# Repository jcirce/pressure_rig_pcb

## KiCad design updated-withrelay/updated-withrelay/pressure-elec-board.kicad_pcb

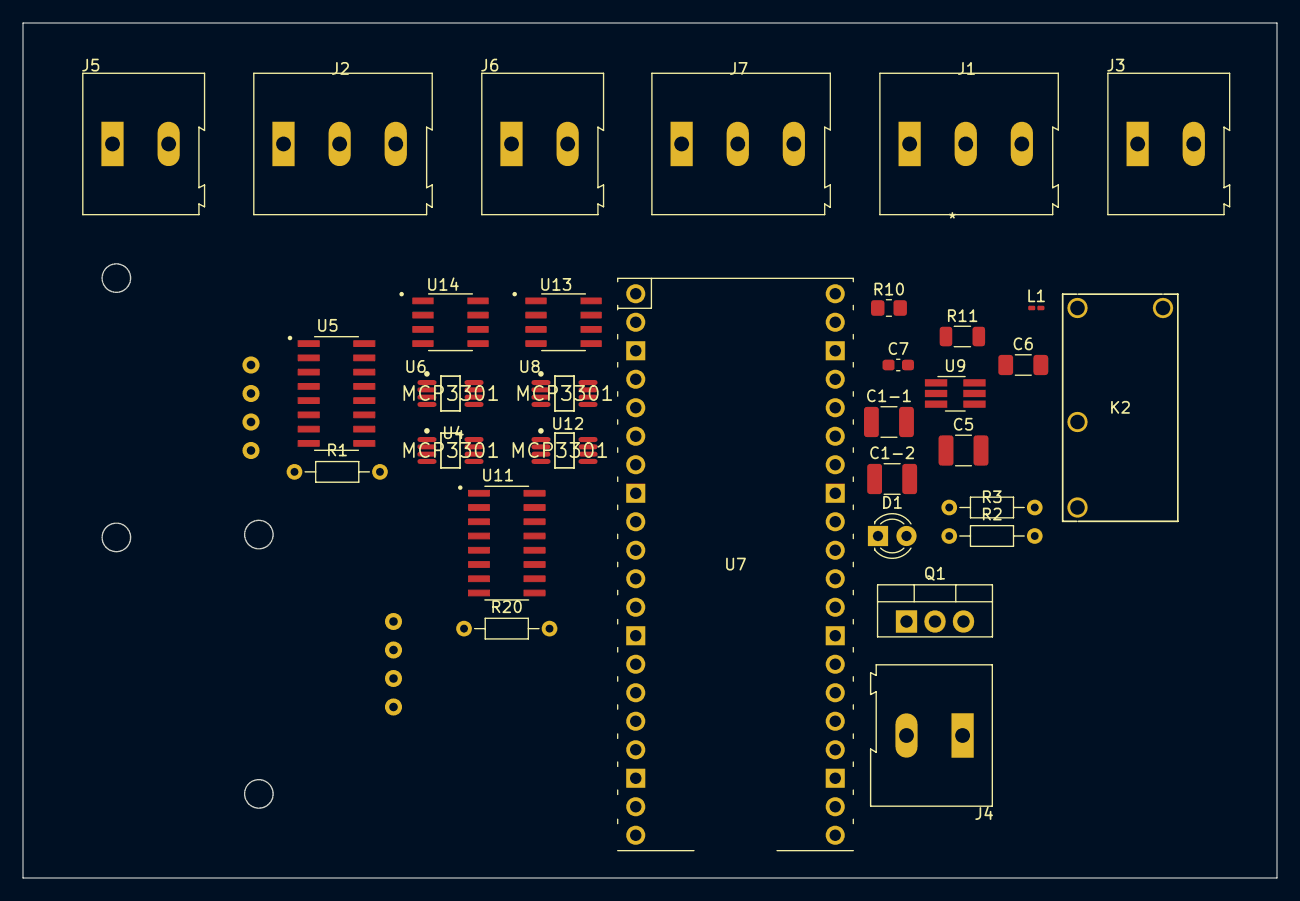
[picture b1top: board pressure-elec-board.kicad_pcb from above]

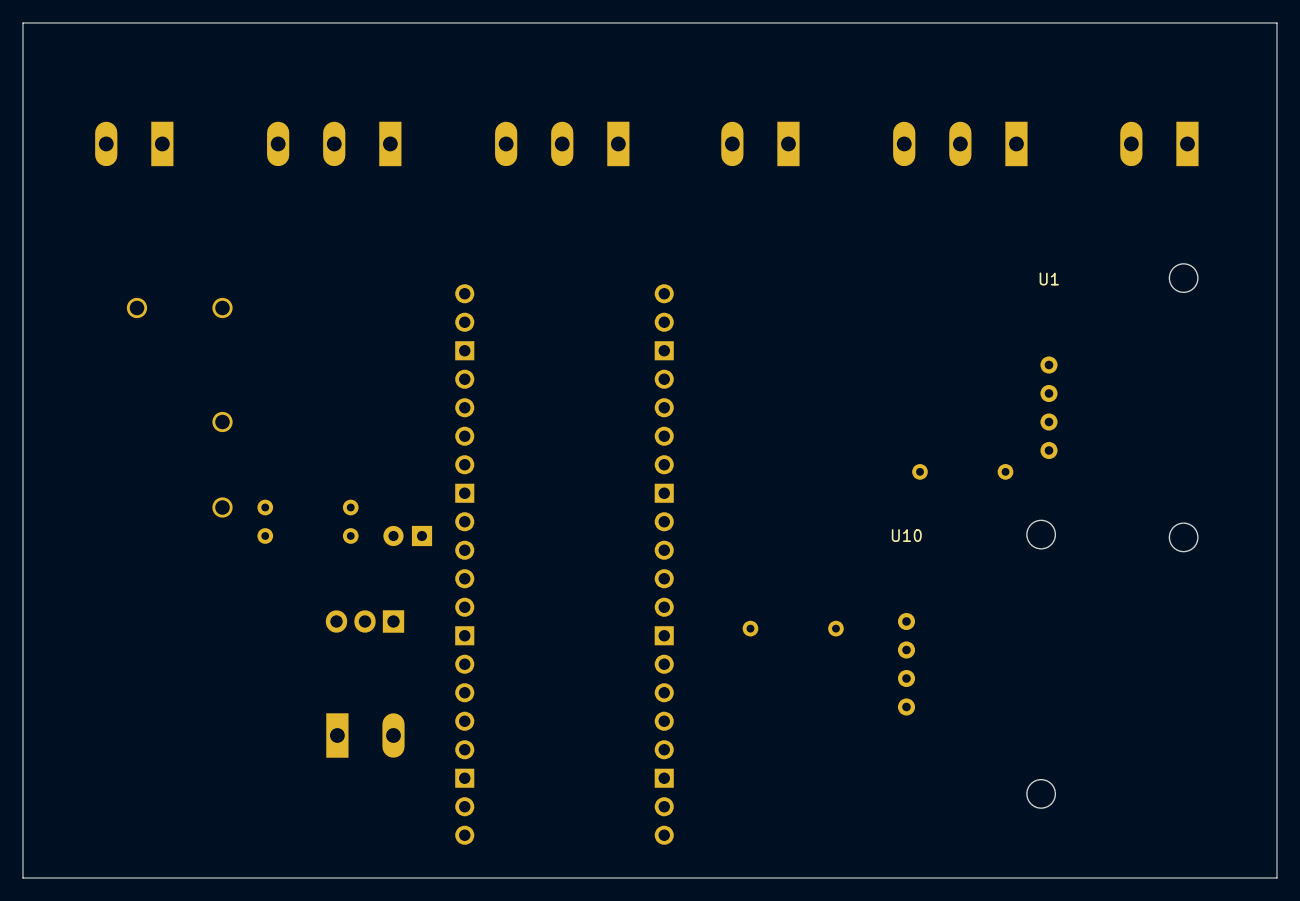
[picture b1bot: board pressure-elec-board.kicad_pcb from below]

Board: 2 copper layers, 111.7 x 76.2 mm, 34 parts (2 on the bottom side), 32 nets, no tracks yet.

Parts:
C1-1, C1-2: 22μ; C_1210_3225Metric_Pad1.33x2.70mm_HandSolder
C5: 10μ; C_1210_3225Metric_Pad1.33x2.70mm_HandSolder
C6: 0.1μ; C_1206_3216Metric_Pad1.33x1.80mm_HandSolder
C7: 47p; C_0603_1608Metric_Pad1.08x0.95mm_HandSolder
D1: LED; LED_D3.0mm
J1, J2, J7: Screw_Terminal_01x03; TerminalBlock_Altech_AK300-3_P5.00mm
J3, J4, J5, J6: Screw_Terminal_01x03; TerminalBlock_Altech_AK300-2_P5.00mm
K2: ALQ305; RELAY_ALQ3_PAN
L1: 4.7u; L_0201_0603Metric_Pad0.64x0.40mm_HandSolder
Q1: IRF540N; TO-220-3_Vertical
R1, R20: 810; R_Axial_DIN0204_L3.6mm_D1.6mm_P7.62mm_Horizontal
R2: 10k; R_Axial_DIN0204_L3.6mm_D1.6mm_P7.62mm_Horizontal
R3: 220; R_Axial_DIN0204_L3.6mm_D1.6mm_P7.62mm_Horizontal
R10: 158k; R_0805_2012Metric_Pad1.20x1.40mm_HandSolder
R11: 30.1k; R_1206_3216Metric
U1, U10: mpx2200; MPX2200
U4, U6, U8, U12: MCP3301; Microchip-MCP3301-BI_MS-Level_B
U5, U11: INA125P; SOIC127P600X175-16N
U7: PicoW; RPi_Pico_SMD_TH
U9: AP63300WU-7; TSOT-23-6_HandSoldering
U13, U14: MCP4921-EP; SOIC127P600X175-8N

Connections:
3.3V: U7.36 (3V3), U13.1 (VDD), U13.6 (VrefA), U14.1 (VDD), U14.6 (VrefA)
5V: D1.2 (A), J4.1, U1.3 (V_supply), U4.1 (Vref), U4.8 (Vdd), U5.1 (V+), U5.2 (~SLEEP), U6.1 (Vref), U6.8 (Vdd), U8.1 (Vref), U8.8 (Vdd), U10.3 (V_supply), U11.1 (V+), U11.2 (~SLEEP), U12.1 (Vref), U12.8 (Vdd)
12V: C5.1, J1.1, U9.2 (EN), U9.3 (VIN)
+5V: C1-1.1, C1-2.1, C7.2, L1.2, R10.2, U7.39 (VSYS)
ADC_1_ACTIVE: U6.5 (~CS/SHDN), U7.15 (GPIO11), U8.5 (~CS/SHDN), U12.5 (~CS/SHDN)
ADC_2_ACTIVE: U4.5 (~CS/SHDN), U7.14 (GPIO10)
CLK: U4.7 (CLK), U6.7 (CLK), U7.4 (GPIO2), U7.9 (GPIO6), U8.7 (CLK), U12.7 (CLK), U13.3 (SCK), U14.3 (SCK)
DAC_ACTIVE: U13.2 (~CS), U14.2 (~CS)
GND: C1-1.2, C1-2.2, C5.2, J1.2, J5.2, J6.2, Q1.3 (S), R2.2, R3.2, R11.2, U1.1 (GND), U4.3 (IN-), U4.4 (Vss), U5.3 (V-), U5.5 (IAREF), U5.12 (VREFCOM), U6.3 (IN-), U6.4 (Vss), U7.3 (GND), U7.8 (GND), U7.13 (GND), U7.18 (GND), U7.23 (GND), U7.28 (GND), U8.3 (IN-), U8.4 (Vss), U9.4 (GND), U10.1 (GND), U11.3 (V-), U11.5 (IAREF), U11.12 (VREFCOM), U12.3 (IN-), U12.4 (Vss), U13.5 (~LDAC), U13.7 (AVSS), U14.5 (~LDAC), U14.7 (AVSS)
GPIO5: Q1.1 (G), R2.1, U7.29 (GPIO22)
MISO_3V_reg1: U7.6 (GPIO4), U8.6 (Dout)
MISO_3V_reg2: U4.6 (Dout), U7.11 (GPIO8)
MOSI_reg1: U7.5 (GPIO3), U14.4 (SDI)
MOSI_reg2: U7.10 (GPIO7), U13.4 (SDI)
unnamed: D1.1 (K), R3.1
unnamed: J4.2, Q1.2 (D)
unnamed: R1.1, U5.8 (RG)
unnamed: R1.2, U5.9 (RG)
unnamed: R20.1, U11.8 (RG)
unnamed: R20.2, U11.9 (RG)
unnamed: U1.2 (+out), U5.6 (V+IN)
unnamed: U1.4 (-out), U5.7 (V-IN)
unnamed: U5.10 (VO), U5.11 (SENSE), U6.2 (IN+)
unnamed: C6.1, U9.6 (BST)
unnamed: C7.1, R10.1, R11.1, U9.1 (FB)
unnamed: C6.2, L1.1, U9.5 (SW)
unnamed: U10.2 (+out), U11.6 (V+IN)
unnamed: U10.4 (-out), U11.7 (V-IN)
unnamed: U11.10 (VO), U11.11 (SENSE), U12.2 (IN+)
pressure_input1: J2.1, J5.1, U14.8 (VoutA)
pressure_input2: J6.1, J7.1, U13.8 (VoutA)
relay_module_input: J1.3, J3.1

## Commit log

2023-04-15 Pressure Rig PcB w/ Pico. Using DC DC converter and has estop
2023-04-15 Pressure Rig with Pico
2023-06-21 Modified pcb to include two pressure rigs
2023-08-21 current iteration of pcb b4 review
